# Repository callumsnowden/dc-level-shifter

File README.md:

# 0-5 to 0-10V Level Shifter

## Introduction
This board is a simple op-amp based level shifter that doubles the input voltage. Options have been provided for termination and all IO is ESD protected.

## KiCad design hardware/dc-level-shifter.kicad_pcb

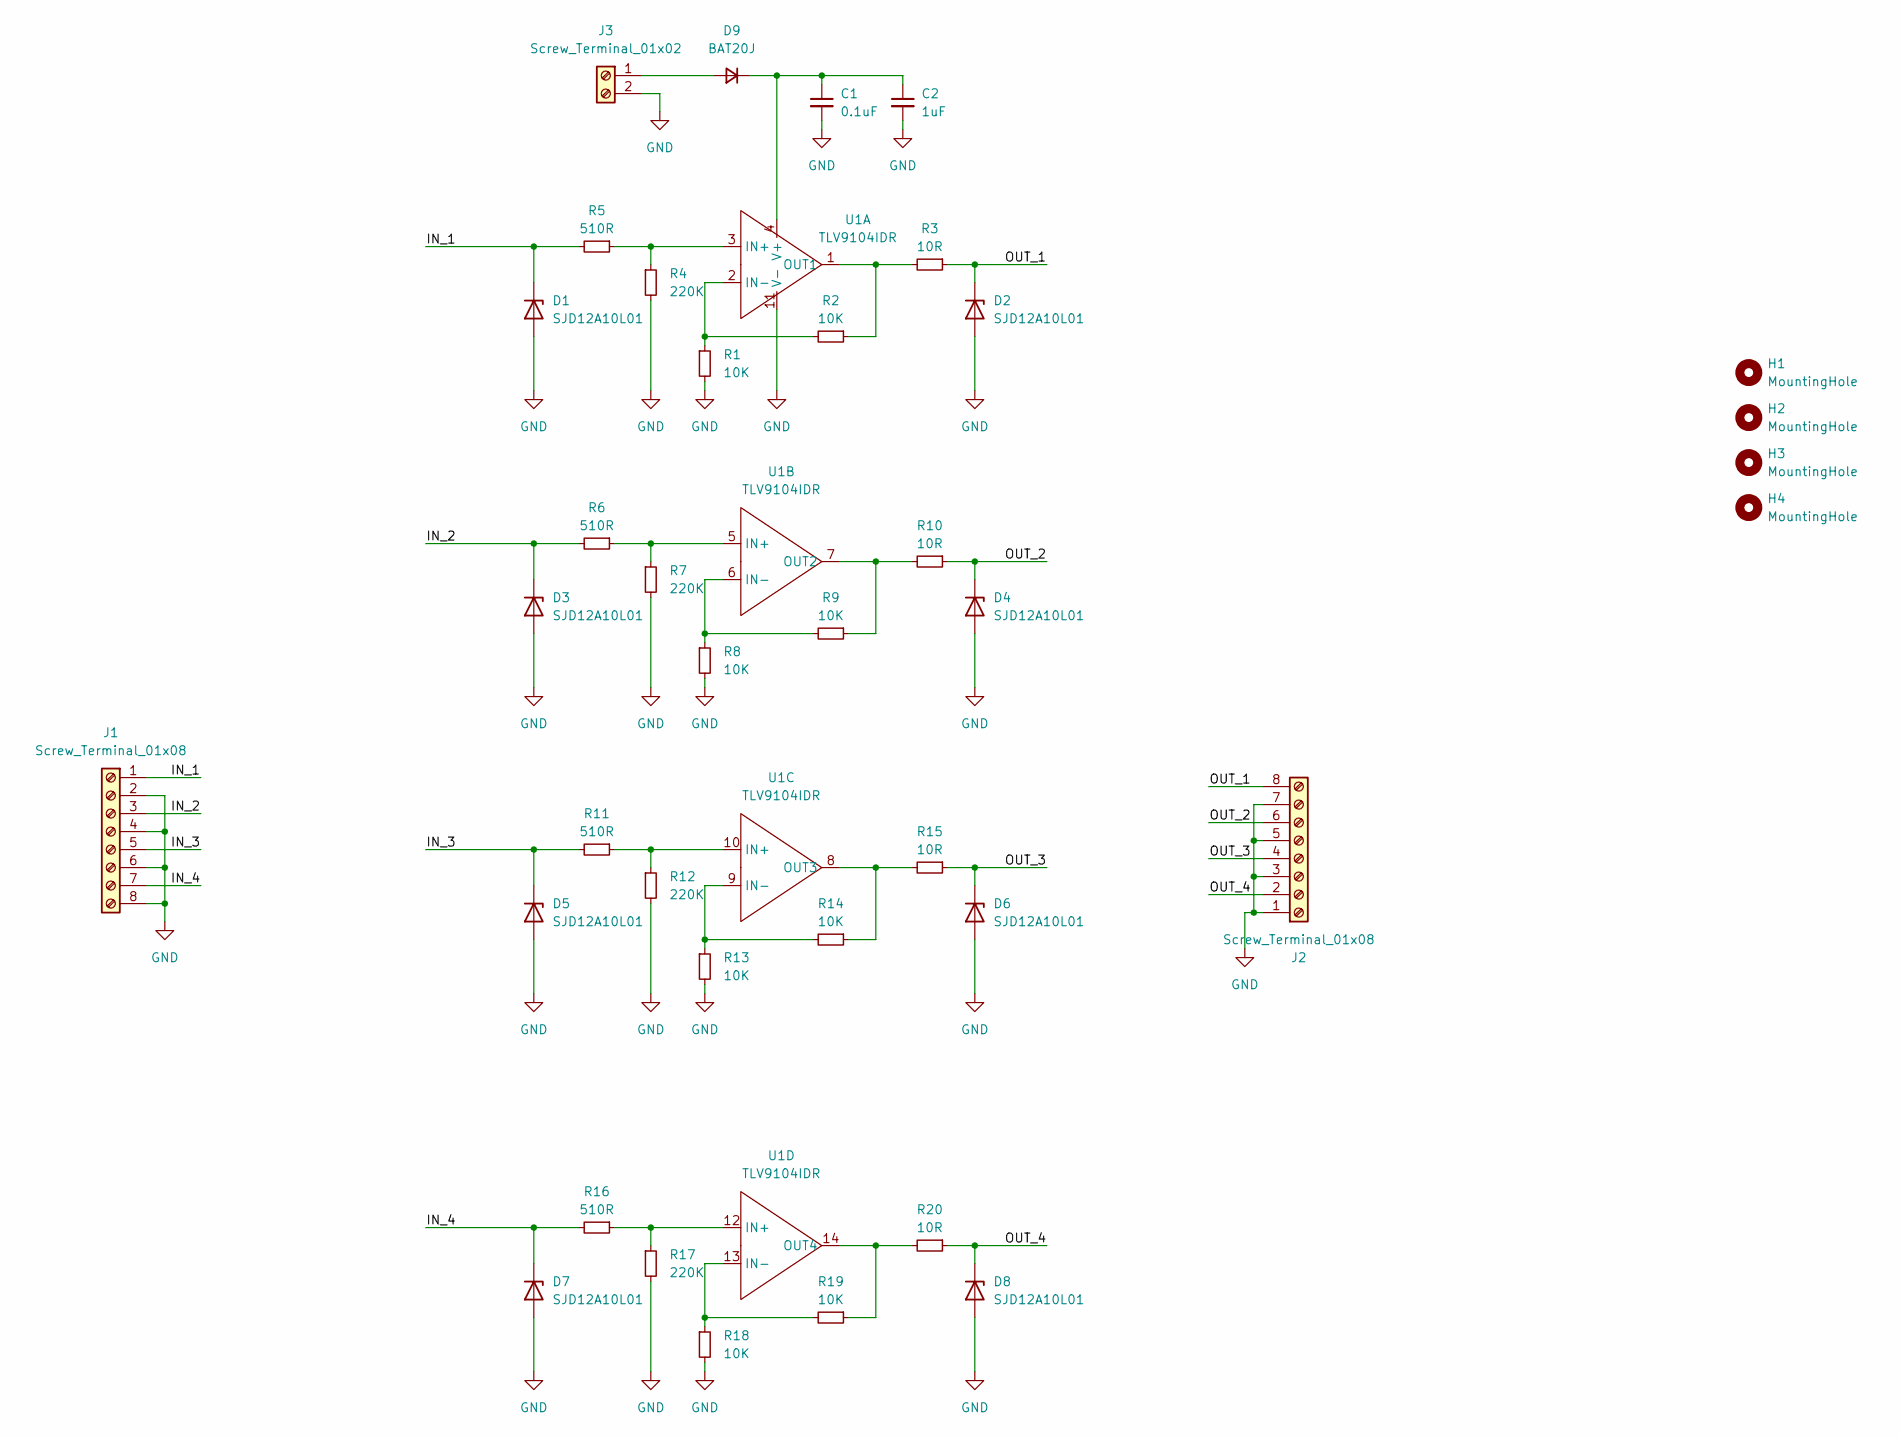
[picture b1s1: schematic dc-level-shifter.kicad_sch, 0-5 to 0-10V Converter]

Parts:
C1: 0.1uF; C_0603_1608Metric
C2: 1uF; C_0603_1608Metric
D1, D2, D3, D4, D5, D6, D7, D8: SJD12A10L01; D_SOD-123
D9: BAT20J; D_SOD-323
H1, H2, H3, H4: MountingHole; MountingHole_3.2mm_M3_DIN965
J1, J2: Screw_Terminal_01x08; TerminalBlock_Phoenix_MKDS-1,5-8-5.08_1x08_P5.08mm_Horizont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; ManufacturerPartNumber 1729186
J3: Screw_Terminal_01x02; TerminalBlock_Phoenix_MKDS-1,5-2-5.08_1x02_P5.08mm_Horizont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
R1, R2, R8, R9, R13, R14, R18, R19: 10K; R_0603_1608Metric
R3, R10, R15, R20: 10R; R_0603_1608Metric
R4, R7, R12, R17: 220K; R_0603_1608Metric
R5, R6, R11, R16: 510R; R_0603_1608Metric
U1: TLV9104IDR; SOIC-14_3.9x8.7mm_P1.27mm; ManufacturerPartNumber TLV9104IDR

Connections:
/IN_1: D1.1 (K), J1.1, R5.2
/IN_2: D3.1 (K), J1.3, R6.2
/IN_3: D5.1 (K), J1.5, R11.2
/IN_4: D7.1 (K), J1.7, R16.2
/OUT_1: D2.1 (K), J2.8, R3.1
/OUT_2: D4.1 (K), J2.6, R10.1
/OUT_3: D6.1 (K), J2.4, R15.1
/OUT_4: D8.1 (K), J2.2, R20.1
GND: C1.2, C2.2, D1.2 (A), D2.2 (A), D3.2 (A), D4.2 (A), D5.2 (A), D6.2 (A), D7.2 (A), D8.2 (A), J1.2, J1.4, J1.6, J1.8, J2.1, J2.3, J2.5, J2.7, J3.2, R1.2, R4.2, R7.2, R8.2, R12.2, R13.2, R17.2, R18.2, U1.11 (V-)
unnamed: D9.2 (A), J3.1
unnamed: C1.1, C2.1, D9.1 (K), U1.4 (V+)
unnamed: R4.1, R5.1, U1.3 (IN+)
unnamed: R1.1, R2.2, U1.2 (IN-)
unnamed: R2.1, R3.2, U1.1 (OUT1)
unnamed: R6.1, R7.1, U1.5 (IN+)
unnamed: R8.1, R9.2, U1.6 (IN-)
unnamed: R9.1, R10.2, U1.7 (OUT2)
unnamed: R11.1, R12.1, U1.10 (IN+)
unnamed: R13.1, R14.2, U1.9 (IN-)
unnamed: R14.1, R15.2, U1.8 (OUT3)
unnamed: R16.1, R17.1, U1.12 (IN+)
unnamed: R18.1, R19.2, U1.13 (IN-)
unnamed: R19.1, R20.2, U1.14 (OUT4)

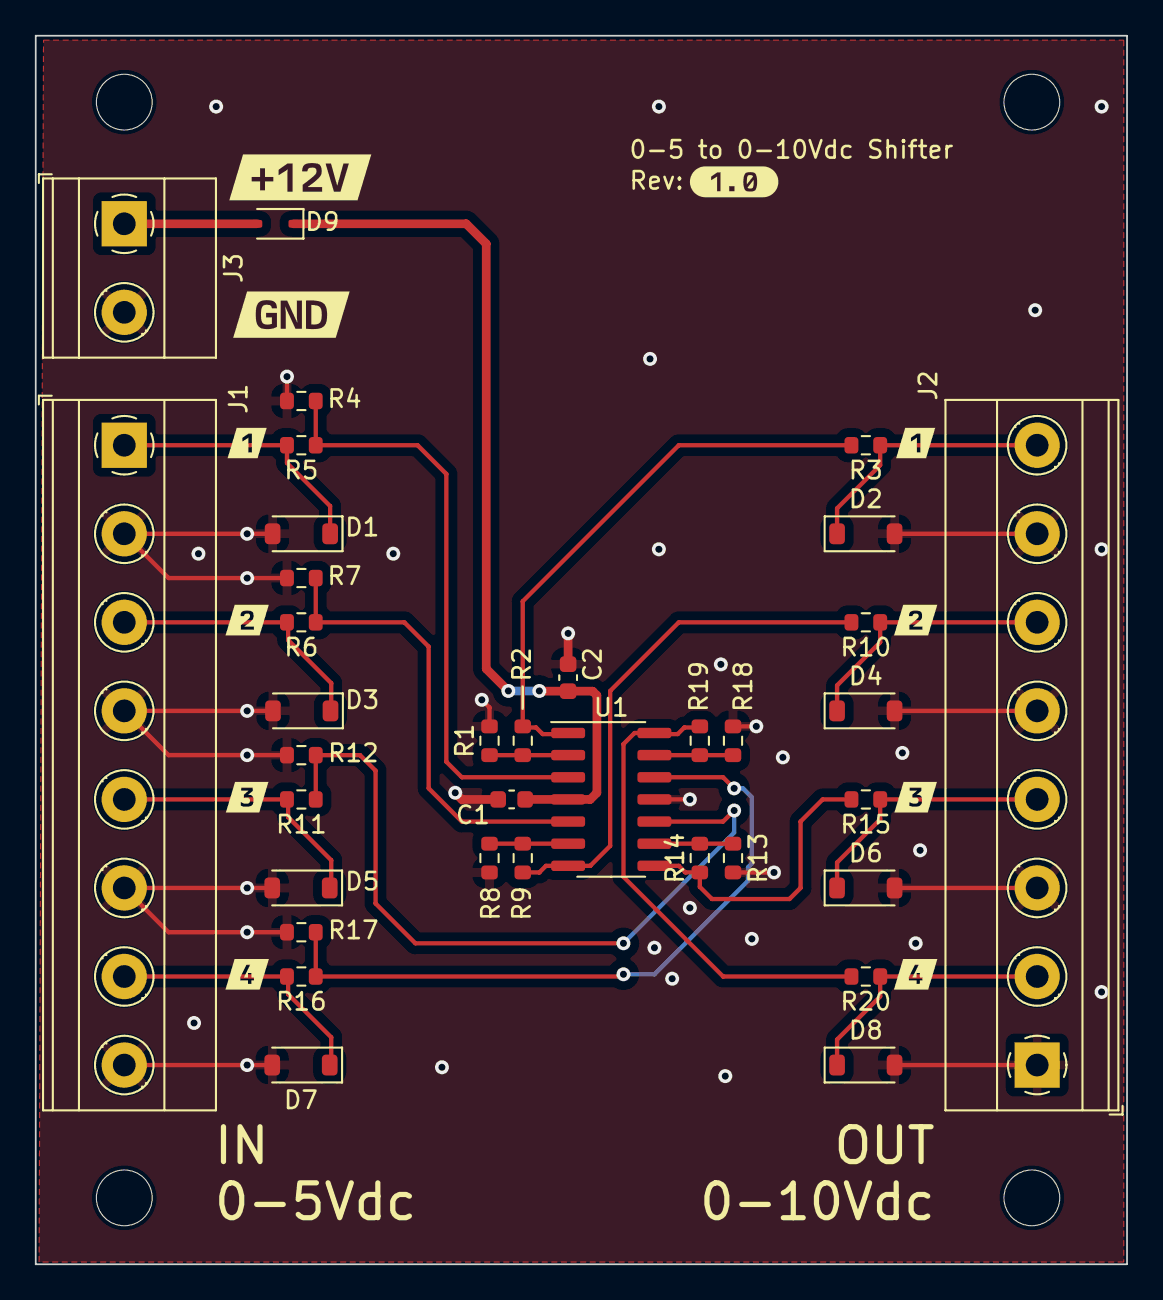
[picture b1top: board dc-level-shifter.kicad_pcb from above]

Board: 2 copper layers, 62.6 x 70.5 mm, 50 parts (0 on the bottom side), 23 nets.

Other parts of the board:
kibuzzard-65C234C2: G***; kibuzzard-65C234C2
kibuzzard-65C2346D, kibuzzard-65C2346D#2: G***; kibuzzard-65C2346D
kibuzzard-65C2349A, kibuzzard-65C2349A#2: G***; kibuzzard-65C2349A
kibuzzard-65C23431: G***; kibuzzard-65C23431
kibuzzard-65C23448: G***; kibuzzard-65C23448
kibuzzard-65C23458, kibuzzard-65C23458#2: G***; kibuzzard-65C23458
kibuzzard-65C23477, kibuzzard-65C23477#2: G***; kibuzzard-65C23477

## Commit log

2024-02-06 Rev 1.0 design
    Rev 1.0 design of the quad channel 0-5V to 0-10V level shifter
2024-03-25 Add STEP file
